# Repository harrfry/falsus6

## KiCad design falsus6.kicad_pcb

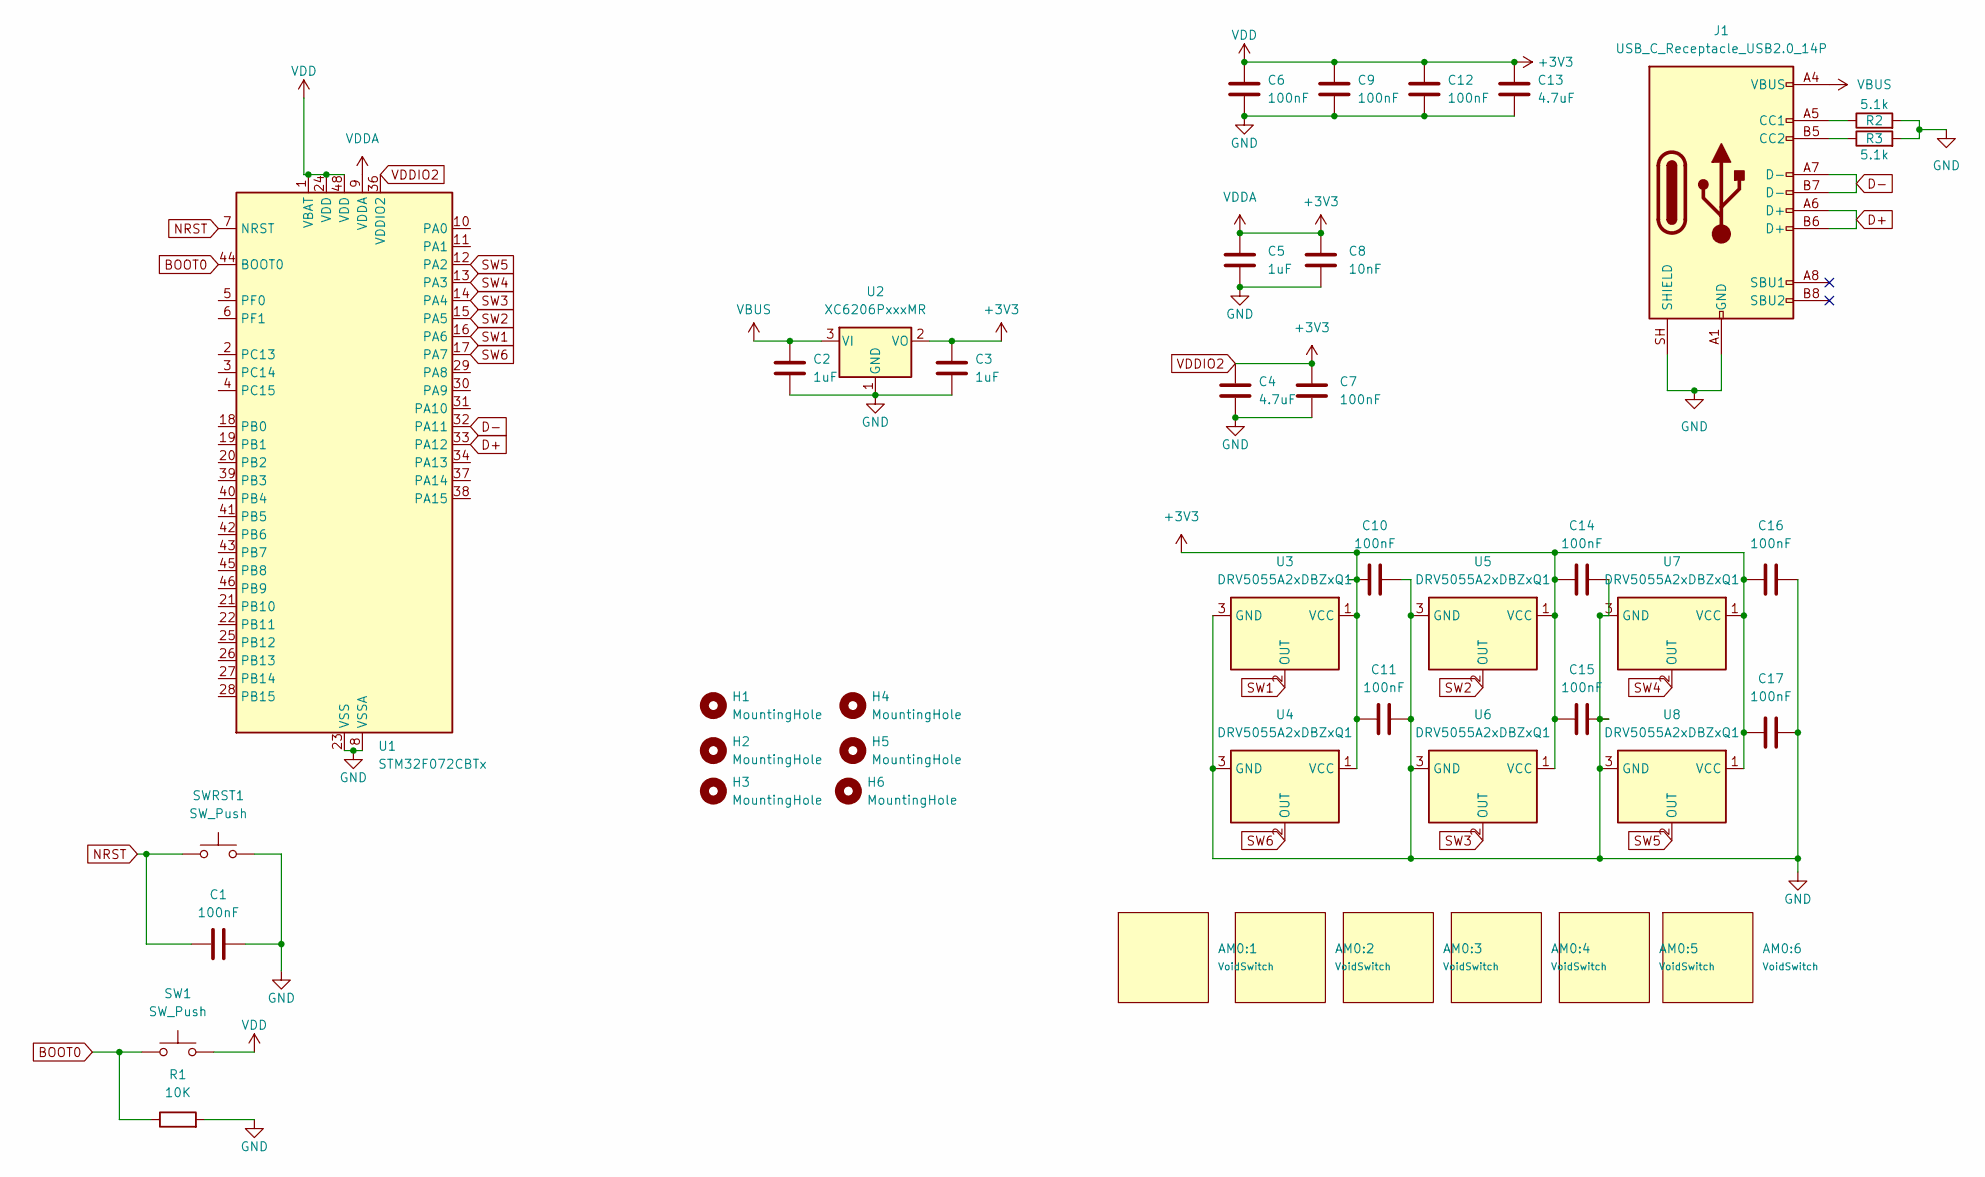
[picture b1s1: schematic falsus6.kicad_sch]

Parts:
AM0:1, AM0:6: VoidSwitch; SW_Cherry_MX_2.75u_PCB
AM0:2, AM0:3, AM0:4, AM0:5: VoidSwitch; SW_Cherry_MX_1.00u_PCB
C1, C6, C7, C9, C10, C11, C12, C14, C15, C16, C17: 100nF; C_0805_2012Metric_Pad1.18x1.45mm_HandSolder
C2, C3, C5: 1uF; C_0805_2012Metric_Pad1.18x1.45mm_HandSolder
C4, C13: 4.7uF; C_0805_2012Metric_Pad1.18x1.45mm_HandSolder
C8: 10nF; C_0805_2012Metric_Pad1.18x1.45mm_HandSolder
H1, H2, H3, H4, H5, H6: MountingHole; MountingHole_3.4mm
J1: USB_C_Receptacle_USB2.0_14P; USB_C_Receptacle_HRO_TYPE-C-31-M-12; LCSC C165948
R1: 10K; R_0805_2012Metric_Pad1.20x1.40mm_HandSolder
R2, R3: 5.1k; R_0805_2012Metric_Pad1.20x1.40mm_HandSolder; LCSC C2907114
SW1: SW_Push; Panasonic_EVQPUL_EVQPUC
SWRST1: SW_Push; Panasonic_EVQPUL_EVQPUC
U1: STM32F072CBTx; LQFP-48_7x7mm_P0.5mm
U2: XC6206PxxxMR; SOT-23-3
U3, U4, U5, U6, U7, U8: DRV5055A2xDBZxQ1; SOT-23

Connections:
BOOT0: R1.1, SW1.1, U1.44 (BOOT0)
D+: J1.A6 (D+), J1.B6 (D+), U1.33 (PA12)
D-: J1.A7 (D-), J1.B7 (D-), U1.32 (PA11)
GND: C1.2, C2.2, C3.2, C4.2, C5.2, C6.2, C7.2, C8.2, C9.2, C10.2, C11.2, C12.2, C13.2, C14.2, C15.2, C16.2, C17.2, J1.A1 (GND), J1.A12 (GND), J1.B1 (GND), J1.B12 (GND), J1.SH (SHIELD), R1.2, R2.2, R3.2, SWRST1.2, U1.8 (VSSA), U1.23 (VSS), U1.35 (VSS), U1.47 (VSS), U2.1 (GND), U3.3 (GND), U4.3 (GND), U5.3 (GND), U6.3 (GND), U7.3 (GND), U8.3 (GND)
NRST: C1.1, SWRST1.1, U1.7 (NRST)
unnamed: J1.A5 (CC1), R2.1
unnamed: J1.B5 (CC2), R3.1
SW1: U1.16 (PA6), U3.2 (OUT)
SW2: U1.15 (PA5), U5.2 (OUT)
SW3: U1.14 (PA4), U6.2 (OUT)
SW4: U1.13 (PA3), U7.2 (OUT)
SW5: U1.12 (PA2), U8.2 (OUT)
SW6: U1.17 (PA7), U4.2 (OUT)
VBUS: C2.1, J1.A4 (VBUS), J1.A9 (VBUS), J1.B4 (VBUS), J1.B9 (VBUS), U2.3 (VI)
VDDIO2: C3.1, C4.1, C5.1, C6.1, C7.1, C8.1, C9.1, C10.1, C11.1, C12.1, C13.1, C14.1, C15.1, C16.1, C17.1, SW1.2, U1.1 (VBAT), U1.9 (VDDA), U1.24 (VDD), U1.36 (VDDIO2), U1.48 (VDD), U2.2 (VO), U3.1 (VCC), U4.1 (VCC), U5.1 (VCC), U6.1 (VCC), U7.1 (VCC), U8.1 (VCC)

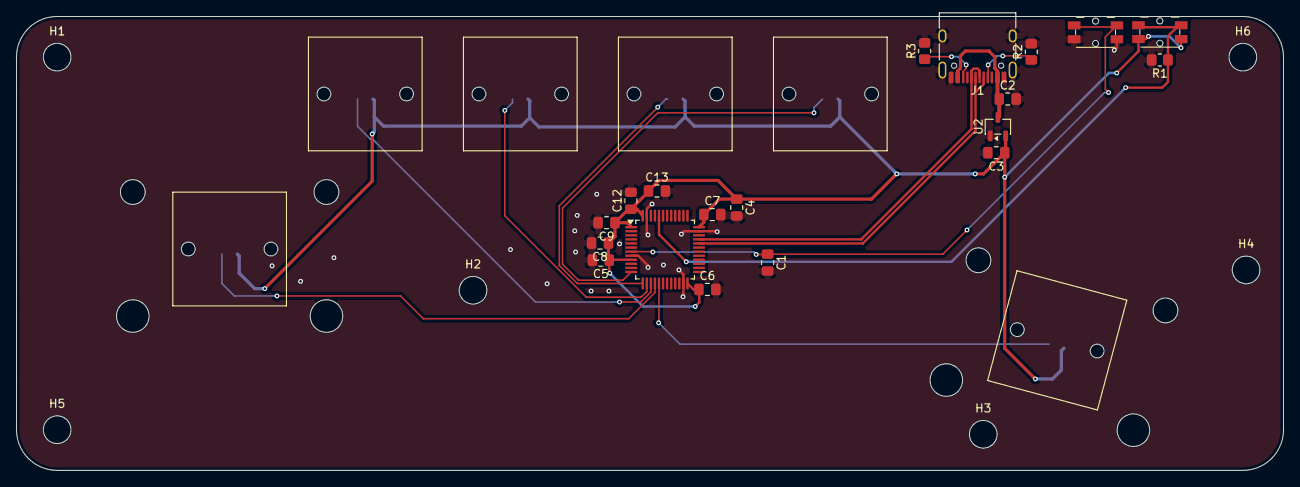
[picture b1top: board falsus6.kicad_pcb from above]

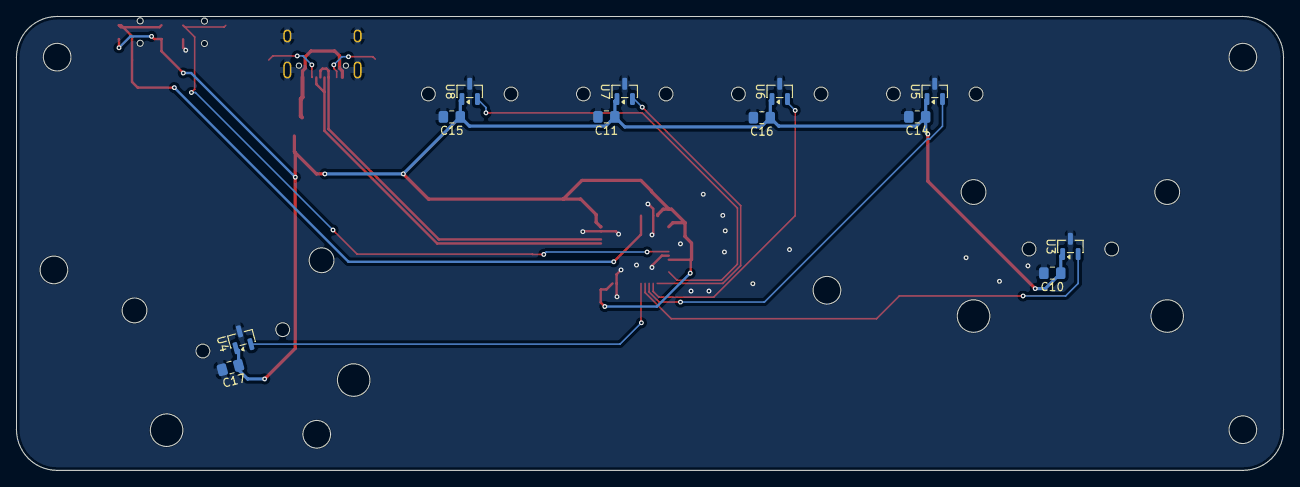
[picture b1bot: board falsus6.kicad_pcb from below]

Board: 2 copper layers, 155.7 x 55.8 mm, 43 parts (12 on the bottom side), 15 nets.

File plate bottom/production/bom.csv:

Designator,Footprint,Quantity,Value,LCSC Part #
"C1, C10, C11, C12, C14, C15, C16, C17, C6, C7, C9",0805,11,100nF,
"C13, C4",0805,2,4.7uF,
"C2, C3, C5",0805,3,1uF,
C8,0805,1,10nF,
J1,USB_C_Receptacle_HRO_TYPE-C-31-M-12,1,USB_C_Receptacle_USB2.0_14P,C165948
R1,0805,1,10K,
"R2, R3",0805,2,5.1k,C2907114
"SW1, SWRST1",Panasonic_EVQPUL_EVQPUC,2,SW_Push,
U1,LQFP-48_7x7mm_P0.5mm,1,STM32F072CBTx,
U2,SOT-23-3,1,XC6206PxxxMR,
"U3, U4, U5, U6, U7, U8",SOT-23,6,DRV5055A2xDBZxQ1,
